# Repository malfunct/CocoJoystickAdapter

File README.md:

# CocoJoystickAdapter
Adapter to connect USB devices, such as gamepad or mouse,  to Tandy Color Computer joystick port.

Gerbers for shield PCB available in Shield Eagle Project directory. I have used https://jlcpcb.com/ to produce the boards in the past but any board house should be fine.

Components for the shield are listed in PartsList.txt

Arduino code for wireless xbox 360 controllers using wireless xbox 360 USB dongle is in the XBOX_360_wireless_arduino_code directory

Arduino code for wired xbox 360 controllers is in the XBOX_360_arduino_code directory

Make sure you have the libraries listed in Dependencies.txt installed for your Arduino IDE as well as configuring it for Arduino Uno R3 then open the correct ino file (wired or wireless) to match the controller you plan to use and compile and push to your Arduino Uno R3.

I assemble the shields with arduino on the bottom, USB sheild next and Coco Joystick shield on top. I power the arduino through the USB-B connector on the R3 board, plug my xbox controller into the USB sheild and use a straight through 6 pin din to 6 pin din cable to connect the adapter to the coco. A Commodore IEC cable works well for this purpose and are easy to find pre-built.

Have fun with your Coco!

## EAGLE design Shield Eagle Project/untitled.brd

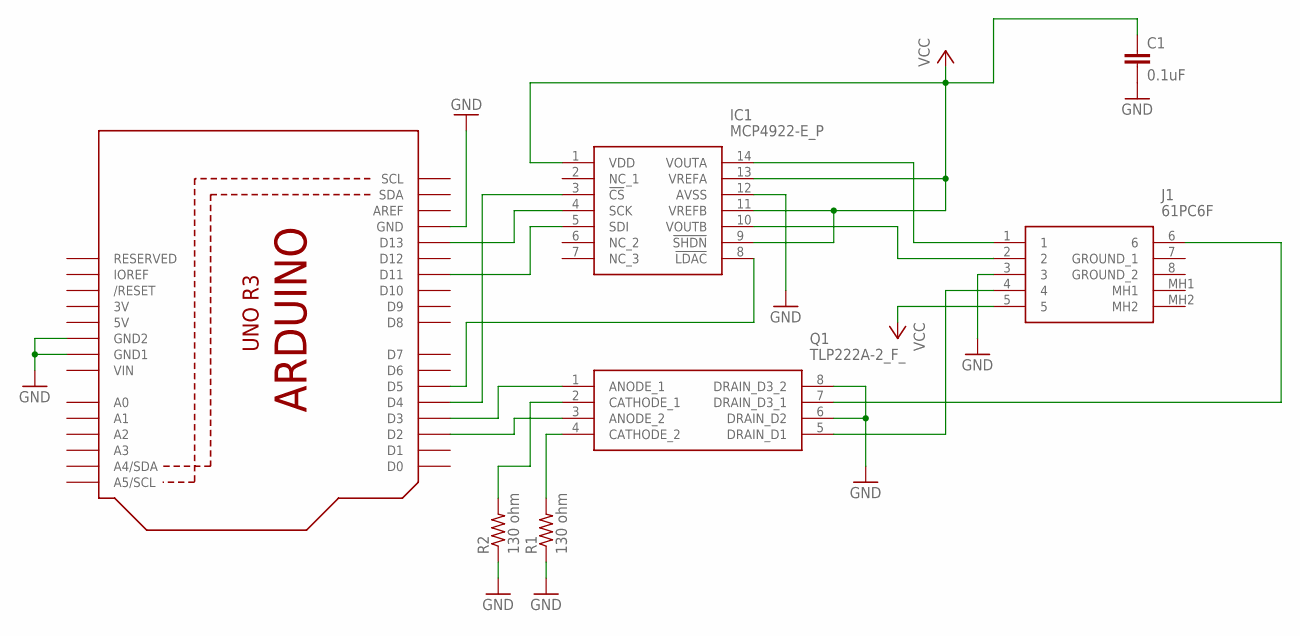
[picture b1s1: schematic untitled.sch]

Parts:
C1: 0.1uF; C050-024X044
IC1: MCP4922-E_P; DIP794W56P254L1905H432Q14N
J1: 61PC6F
Q1: TLP222A-2_F_; DIP762W60P254L966H485Q8N
R1, R2: 130 ohm; 0207/7
U1: ARDUINOR3-BPLACE

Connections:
3V: U1.3V
5V: U1.5V
GND: C1.2, IC1.12 (AVSS), J1.3, Q1.6 (DRAIN_D2), Q1.8 (DRAIN_D3_2), R1.1, R2.1, U1.GND, U1.GND1, U1.GND2
unnamed: IC1.4 (SCK), U1.D13
unnamed: IC1.5 (SDI), U1.D11
unnamed: Q1.4 (CATHODE_2), R1.2
unnamed: IC1.3 (!CS), U1.D4
unnamed: IC1.8 (!LDAC), U1.D5
unnamed: Q1.2 (CATHODE_1), R2.2
unnamed: Q1.1 (ANODE_1), U1.D3
unnamed: Q1.3 (ANODE_2), U1.D2
unnamed: J1.6, Q1.7 (DRAIN_D3_1)
unnamed: J1.4, Q1.5 (DRAIN_D1)
unnamed: IC1.14 (VOUTA), J1.1
unnamed: IC1.10 (VOUTB), J1.2
VCC: C1.1, IC1.1 (VDD), IC1.9 (!SHDN), IC1.11 (VREFB), IC1.13 (VREFA), J1.5
VIN: U1.VIN

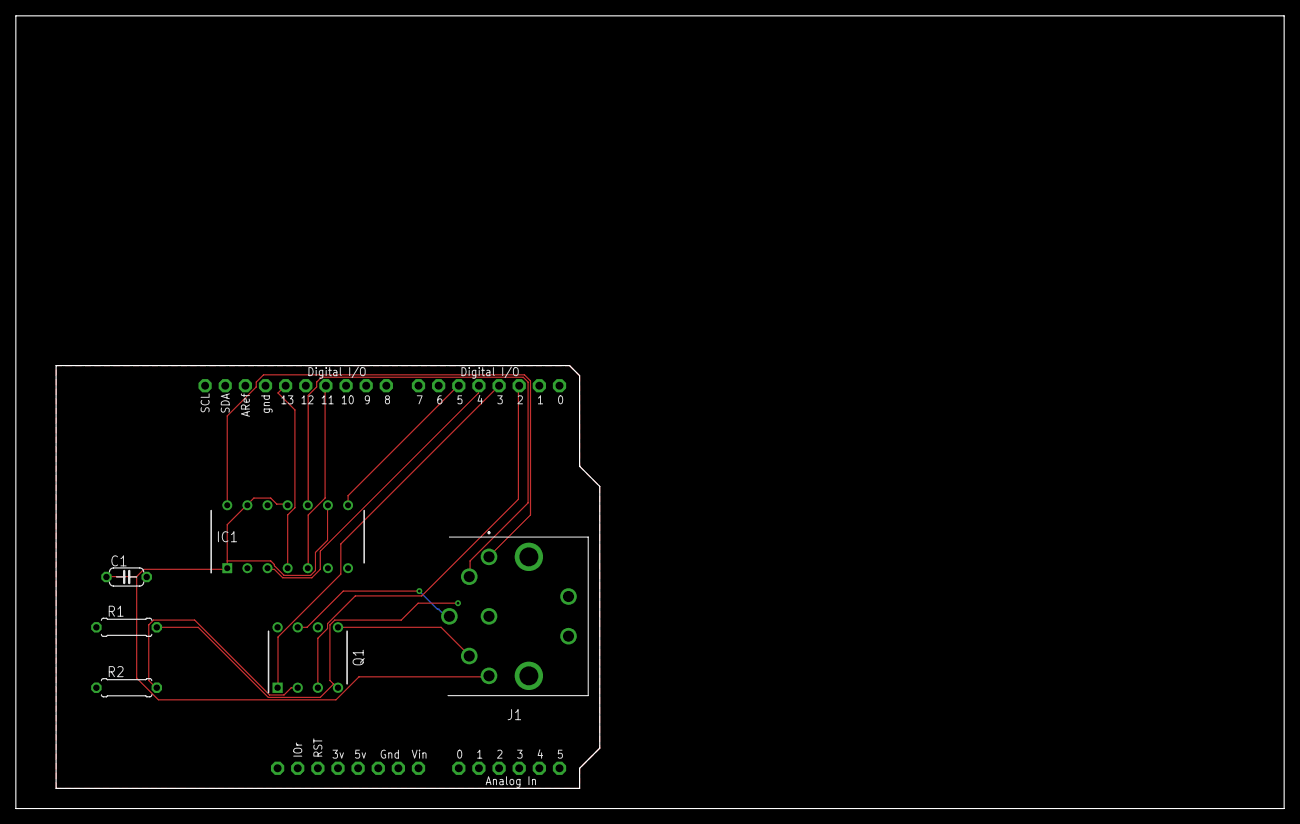
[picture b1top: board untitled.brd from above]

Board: 2 copper layers, 160.0 x 100.0 mm, 7 parts (0 on the bottom side), 14 nets.

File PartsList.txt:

1 - 61PC6F female DIN-6 connector
1 - TLP222A-2 dual solid state relay
1 - MCP4922 dual channel 12bit DAC with SPI
1 - 0.1uF ceramic capcitor
2 - 130 ohm 1/8 watt resistor
1 - 14 pin DIP socket
1 - 8 pin DIP socket
2 - 6 pin single row arduino stackable shield header
2 - 8 pin single row arduino stackable shield header
1 - Arduino Uno R3 (or clone)
1 - Keyes USB Host Shield https://www.fasttech.com/product/1144300-keyes-usb-host-shie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 (other brands did not work for me)

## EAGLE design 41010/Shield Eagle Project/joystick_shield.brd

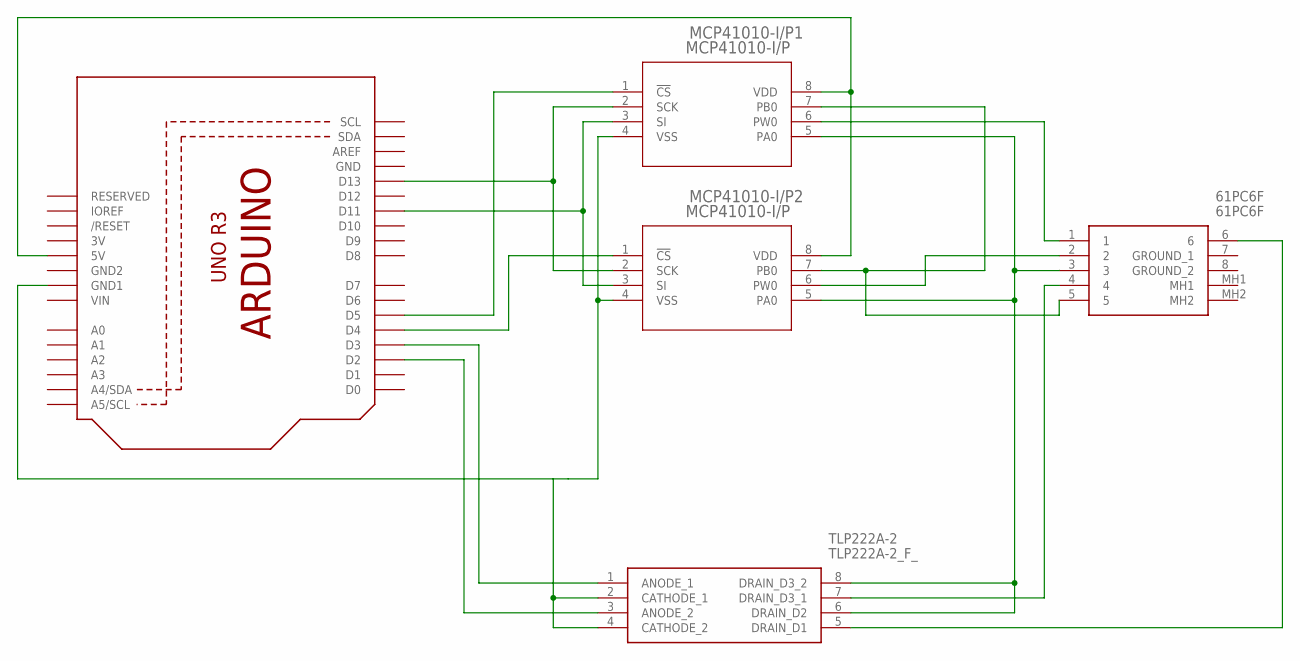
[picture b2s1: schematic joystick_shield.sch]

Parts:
61PC6F: 61PC6F
MCP41010-I/P1, MCP41010-I/P2: MCP41010-I/P; PDIP8_300MC
TLP222A-2: TLP222A-2_F_; DIP762W60P254L966H485Q8N
U3: ARDUINOR3-BPLACE

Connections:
3V: U3.3V
GND: U3.GND
GND2: U3.GND2
unnamed: MCP41010-I/P1.2 (SCK), MCP41010-I/P2.2 (SCK), U3.D13
unnamed: MCP41010-I/P2.1 (!CS), U3.D4
unnamed: MCP41010-I/P1.3 (SI), MCP41010-I/P2.3 (SI), U3.D11
unnamed: MCP41010-I/P1.4 (VSS), MCP41010-I/P2.4 (VSS), TLP222A-2.2 (CATHODE_1), TLP222A-2.4 (CATHODE_2), U3.GND1
unnamed: MCP41010-I/P1.1 (!CS), U3.D5
unnamed: TLP222A-2.1 (ANODE_1), U3.D3
unnamed: MCP41010-I/P1.8 (VDD), MCP41010-I/P2.8 (VDD), U3.5V
unnamed: TLP222A-2.3 (ANODE_2), U3.D2
unnamed: 61PC6F.3, MCP41010-I/P1.5 (PA0), MCP41010-I/P2.5 (PA0), TLP222A-2.6 (DRAIN_D2), TLP222A-2.8 (DRAIN_D3_2)
unnamed: 61PC6F.4, TLP222A-2.7 (DRAIN_D3_1)
unnamed: 61PC6F.5, MCP41010-I/P1.7 (PB0), MCP41010-I/P2.7 (PB0)
unnamed: 61PC6F.6, TLP222A-2.5 (DRAIN_D1)
unnamed: 61PC6F.2, MCP41010-I/P2.6 (PW0)
unnamed: 61PC6F.1, MCP41010-I/P1.6 (PW0)
VIN: U3.VIN

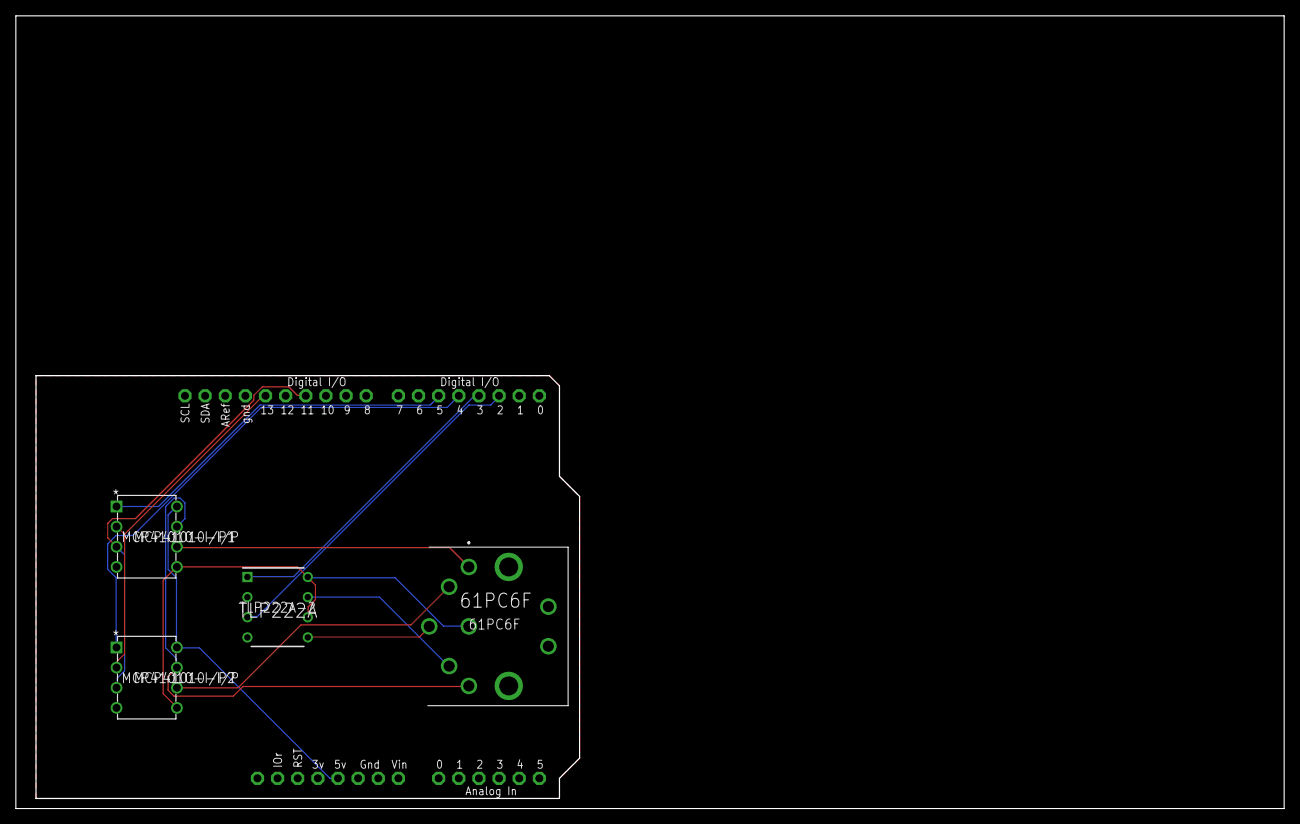
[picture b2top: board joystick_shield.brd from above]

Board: 2 copper layers, 160.0 x 100.0 mm, 5 parts (0 on the bottom side), 14 nets.

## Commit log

2020-06-14 Adding arduino project for Xbox360 controller software.
2020-06-14 Add eagle file for 41010 based arduino shield
2020-06-24 add sketch for mcp4922 based board.
2020-06-24 Add support for using either stick on the xbox controller
2020-06-24 Adding EAGLE files for 4922 based shield.
2020-07-24 Update to latest eagle files.
2020-09-19 Initial commit of xbox wireless controller version of software.
2021-03-01 Parts list for 4922 based joystick adapter.
2021-03-07 Updated parts list with URL to USB Host Shield and added dependancy list for building arduino source.
2021-03-07 Reogranized to make active code easier to find.
2022-05-18 Add current limiting resistor for SSR to meet spec.
2022-05-19 Adding resistor to parts list to match new schematic
2022-05-19 Fixing typo in resistor value from 103 to the correct 130 ohm.
2022-05-23 First draft of 'dual shooter' design
2022-06-03 Using individual resistors between opto isolator and ground to avoid under current conditions that might have happened otherwise.

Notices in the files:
parts and their libraries:
COPYRIGHT: Copyright (C) 2018 Accelerated Designs. All rights reserved
